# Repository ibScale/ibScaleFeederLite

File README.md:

# ibScaleFeederLite

`ibScaleFeederLite` is an updated version of the [Opulo LumenPNP Rev 12 Feeder](https://github.com/opulo-inc/feeder) motherboard with several enhancements.

## What's different from the Rev 12 motherboard

### PCB Stackup
The PCB is a 4-layer stackup with 7628 prepreg. The cost difference is negligible compared to the original 2-layer stackup. This allows for a cleaner layout with improved routing and component placement. The bottom layer of the PCB is kept as a ground layer only with no traces. Since this layer of the PCB is exposed it is very likely to get knicked, scratched, or otherwise damaged by the environment. This prevents any minor damage from affecting the operation of the feeder.

### DC/DC buck converter
The original OnSemi MC34063AD design used a 100µF input and 470µF output electrolytic capacitors. These capacitors are relatively expensive and difficult to source in low-profile heights suitable for the 8mm feeders. The large 100uF input capacitance would also cause arcing during insertion from the inrush current while charging. In addition to this, if the LumenPNP had 50 feeders plugged in the excessive bus capacitance would cause power sag (brown out) or potentially even trip the over-current protection. If the over-current protection does trip then the LumenPNP will boot loop as the 24V DC supply resets.

A Texas Instruments TPS563300 with MLCC capacitors has replaced the original design. The input capacitance has been reduced to 10uF to help prevent arcing during insertion. The reduced capacitance also helps mitigate the excessive bus capacitance start-up issue. A 0.75A PPTC fuse (F1) and diode (D1) have also been added to provide over-current and reverse-current protection.

### RS-485 transceiver
The AD/Maxim MAX3078E transceiver is the single most expensive component on the Opulo Rev12 feeder. Since the LumenPNP only operates at 57600bps there is no need to have an expensive part. The new TI THVD1400D transceiver is about 1/10th the cost and more then adequate for this application.

### Status LED
The RGB status LED has been changed to a Lite-On LTST-S33FBEGW-5A. This LED has a translucent diffuser and is designed for low current applications. It is available from a variety of suppliers and is an overall better quality indicator.

### Buttons
The original buttons were probably one of the biggest pain points on the original Rev12 design. These have been upgraded to Diptronics PTCF-V-T/R with J-hook stems. These switches are larger and available from a variety of suppliers. This along with improved debounce circuitry provide a better user experience.

### SWD connector
The original placement of the SWD connector made it difficult to use commonly available POGO pin clips like the Adafruit 5434. The connector was rotated and moved to the edge of the PCB to make using POGO pin clips easier.

## Hardware overview

| Function | Part |
|---|---|
| MCU | STM32F031C6T6 (Arm Cortex-M0, 48 MHz, 32 KB flash) |
| Motor drivers (Drive / Peel) | 2x TI DRV8837 |
| RS-485 transceiver | TI THVD1400D |
| Buck regulator | TI TPS563300 |
| Status LED | Lite-On LTST-S33FBEGW-5A |
| UP/DOWN/BOOT switches | Diptronics PTCF-V-T/R |

## Repository structure

```
ibScaleFeederLite/
├── ibScaleFeederLite.kicad_pro   KiCad project file
├── ibScaleFeederLite.kicad_pcb   PCB layout
├── ibScaleFeederLite.kicad_sch   Schematic
├── library/                      Project-specific symbols, footprints, and 3D models
└── references/                   Component datasheets
```

## Opening the project

Requires [KiCad](https://www.kicad.org/) 10 or newer. Open `ibScaleFeederLite.kicad_pro` to get started.

All custom symbols, footprints, and 3D models used by the project are included in `library/` and referenced via the project-local `sym-lib-table` and `fp-lib-table`, so no additional library setup is required.

## Bill of materials

Every component includes the manufacturer's name and part number, along with DigiKey, Mouser, and LCSC part numbers. To export a BOM, use KiCad's schematic editor: **Tools → Generate Bill of Materials**.

## License

Released under the [CERN Open Hardware Licence Version 2 - Strongly Reciprocal (CERN-OHL-S-2.0)](LICENSE.txt), consistent with the licensing of the original Opulo LumenPNP hardware it is derived from.

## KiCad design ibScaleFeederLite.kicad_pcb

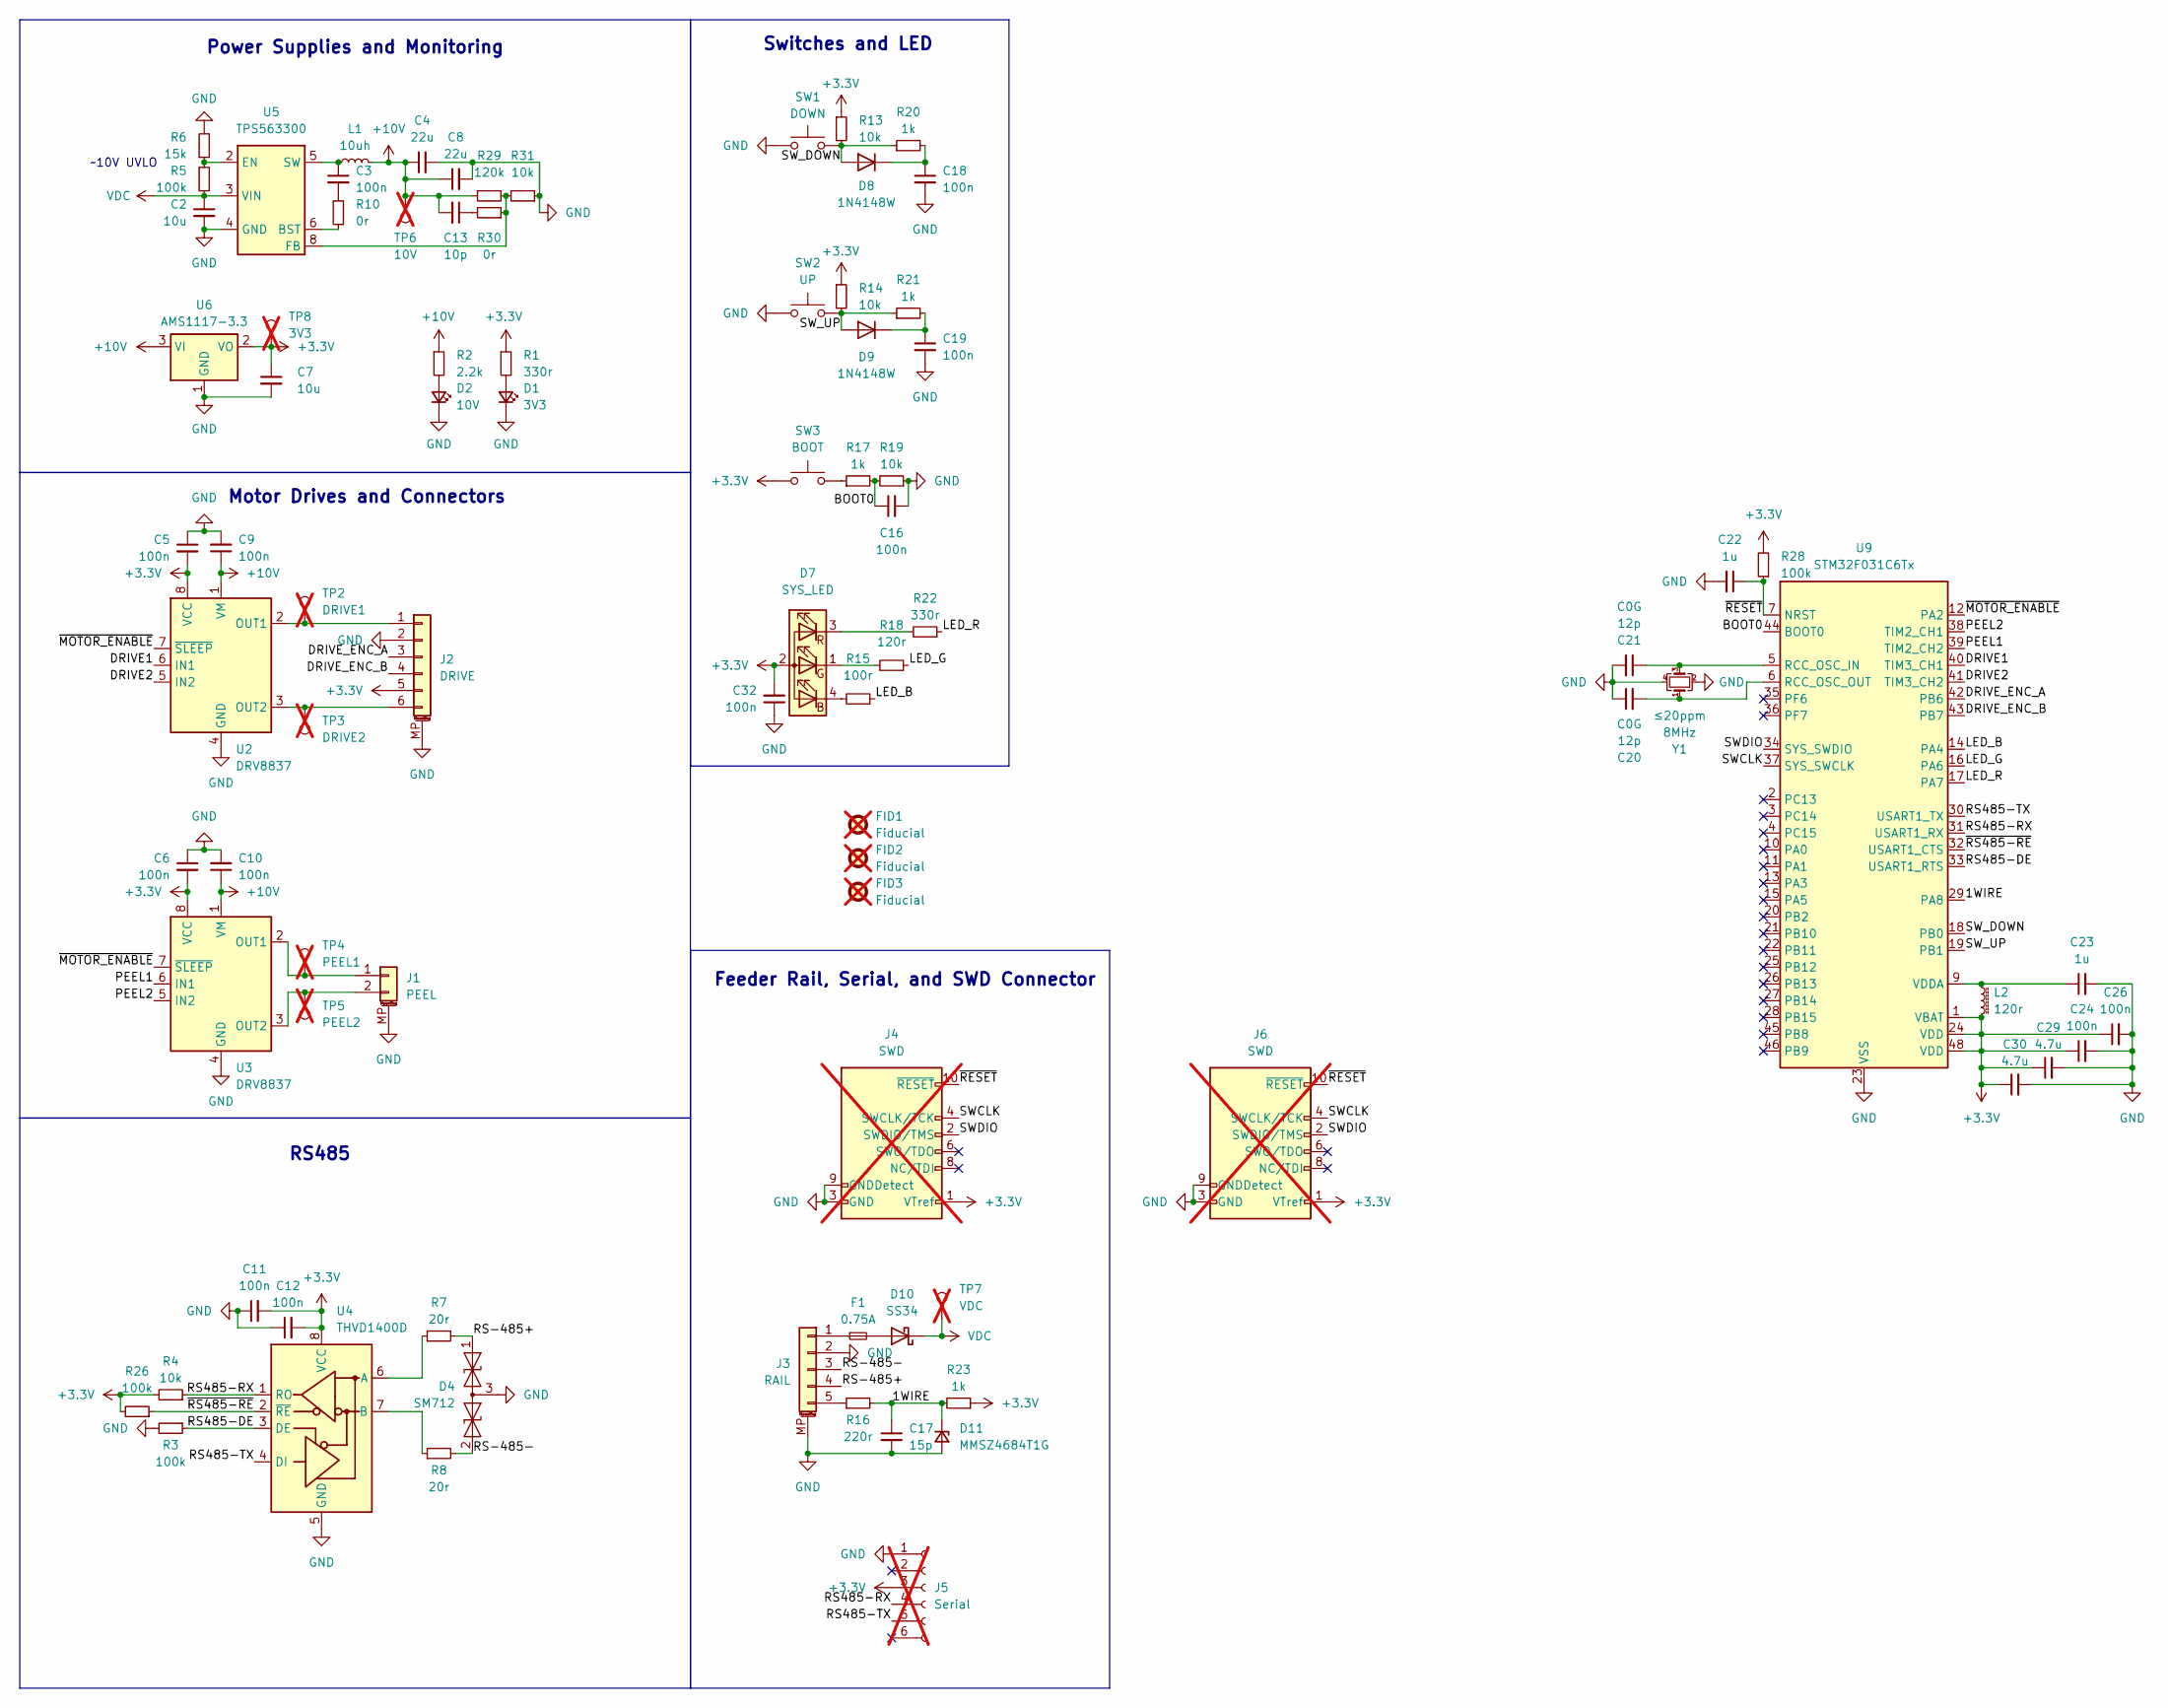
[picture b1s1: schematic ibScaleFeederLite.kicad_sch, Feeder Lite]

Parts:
C2: 10u; C_0805_2012Metric_Pad1.18x1.45mm_HandSolder; Tolerance X5R; Rating 50V; Manufacturer_Part GRM21BR61H106KE43L; Mouser 81-GRM21BR61H106KE3L
C3: 100n; C_0603_1608Metric_Pad1.08x0.95mm_HandSolder; Tolerance X5R; Rating 50V; Manufacturer_Part CC0603KRX7R9BB104; Mouser 603-CC603KRX7R9BB104
C4, C8: 22u; C_0805_2012Metric_Pad1.18x1.45mm_HandSolder; Tolerance X5R; Rating 25V; Manufacturer_Part CL21A226MAQNNNE; Mouser 187-CL21A226MAQNNNE
C5, C6, C9, C10, C11, C12, C24, C26: 100n; C_0603_1608Metric_Pad1.08x0.95mm_HandSolder; Manufacturer_Part CC0603KRX7R9BB104; LCSC C14663
C7: 10u; C_0805_2012Metric_Pad1.18x1.45mm_HandSolder; Manufacturer_Part GRM21BR61H106KE43L; LCSC C440198
C13: 10p; C_0603_1608Metric_Pad1.08x0.95mm_HandSolder; Tolerance CG0; Rating 25V; Manufacturer_Part CL10C100JB8NNNC; Mouser 187-CL10C100JB8NNNC
C16, C18, C19, C32: 100n; C_0603_1608Metric_Pad1.08x0.95mm_HandSolder; Manufacturer_Part CC0603KRX7R9BB104; DigiKey 311-1344-1-ND
C17: 15p; C_0603_1608Metric_Pad1.08x0.95mm_HandSolder; Manufacturer_Part CL10C150JB8NNNC; Mouser 187-CL10C150JB8NNNC
C20, C21: 12p; C_0603_1608Metric_Pad1.08x0.95mm_HandSolder; Rating C0G; Tolerance 1%; Manufacturer_Part CL10C120JB8NNNC; LCSC C38523
C22, C23: 1u; C_0603_1608Metric_Pad1.08x0.95mm_HandSolder; Manufacturer_Part CL10A105KB8NNNC; LCSC C15849
C29, C30: 4.7u; C_0603_1608Metric_Pad1.08x0.95mm_HandSolder; Manufacturer_Part CL10A475KO8NNNC; LCSC C19666
D1: 3V3; LED_0805_2012Metric_Pad1.15x1.40mm_HandSolder; Rating If=20ma, Vf=2.2v; Tolerance green; Manufacturer_Part LG R971-KN-1-0-20-R18; LCSC C2297
D2: 10V; LED_0805_2012Metric_Pad1.15x1.40mm_HandSolder; Rating If=20ma, Vf=2.2v; Tolerance green; Manufacturer_Part LG R971-KN-1-0-20-R18; LCSC C2297
D4: SM712; SOT-23; Manufacturer_Part SM712-02HTG; Mouser 576-SM712-02HTG
D7: SYS_LED; LED-SMD_4P-L3.0-W1.0-SIDE_LTST-S33FBEGW-5A; Manufacturer_Part LTST-S33FBEGW-5A; Mouser 859-LTST-S33FBEGW-5A
D8, D9: 1N4148W; D_SOD-123; Manufacturer_Part 1N4148WGW; LCSC C81598
D10: SS34; D_SMA; Manufacturer_Part SS34ALH; Mouser 821-SS34ALH
D11: MMSZ4684T1G; D_SOD-123; Manufacturer_Part MMSZ4684T1G; Mouser 863-MMSZ4684T1G
F1: 0.75A; Fuse_1812_4532Metric_Pad1.30x3.40mm_HandSolder; Manufacturer_Part PTS181233V075; Mouser 504-PTS181233V075
FID1, FID2, FID3: Fiducial; Fiducial_1mm_Mask2mm; not fitted
J1: PEEL; Molex_PicoBlade_53261-0271_1x02-1MP_P1.25mm_Horizontal; Manufacturer_Part 53261-0271; Mouser 538-53261-0271
J2: DRIVE; Molex_PicoBlade_53261-0671_1x06-1MP_P1.25mm_Horizontal; Manufacturer_Part 53048-0610; Mouser 538-53048-0610
J3: RAIL; 009155005541006; Manufacturer_Part 009155005541006; Mouser 581-009155005541006
J4, J6: SWD; PinHeader_2x05_P1.27mm_Vertical_SMD; not fitted
J5: Serial; PinHeader_1.27mm_1x06_FrictionFit; not fitted
L1: 10uh; L_TDK_VLS6045EX_VLS6045AF; Manufacturer_Part VLS6045EX-100M; Mouser 810-VLS6045EX-100M
L2: 120r; L_0603_1608Metric_Pad1.05x0.95mm_HandSolder; Manufacturer_Part MFBM1V1608-121-R; LCSC C14709
R1: 330r; R_0603_1608Metric_Pad0.98x0.95mm_HandSolder; Manufacturer_Part RC0603FR-13330RL; Mouser 603-RC0603FR-13330RL
R2: 2.2k; R_0603_1608Metric_Pad0.98x0.95mm_HandSolder; Manufacturer_Part RT0603FRE132K2L; LCSC C4190
R3, R26: 100k; R_0603_1608Metric_Pad0.98x0.95mm_HandSolder; Manufacturer_Part RC0603JR-13100KL; LCSC C25803
R4, R13, R14, R19: 10k; R_0603_1608Metric_Pad0.98x0.95mm_HandSolder; Manufacturer_Part RC0603FR-0710KP; LCSC C25804
R5, R28: 100k; R_0603_1608Metric_Pad0.98x0.95mm_HandSolder; Manufacturer_Part RC0603JR-13100KL; Mouser 603-RC0603JR-13100KL
R6: 15k; R_0603_1608Metric_Pad0.98x0.95mm_HandSolder; Manufacturer_Part WR06X153 JTL; Mouser 791-WR06X153JTL
R7, R8: 20r; R_0603_1608Metric_Pad0.98x0.95mm_HandSolder; Manufacturer_Part AC0603JR-0720RL; Mouser 603-AC0603JR-0720RL
R10, R30: 0r; R_0603_1608Metric_Pad0.98x0.95mm_HandSolder; Tolerance 1%; Manufacturer_Part RC0603FR-100RL; Mouser 603-RC0603FR-100RL
R15: 100r; R_0603_1608Metric_Pad0.98x0.95mm_HandSolder; Manufacturer_Part RK73H1JTTD1000F; LCSC C22775
R16: 220r; R_0603_1608Metric_Pad0.98x0.95mm_HandSolder; Manufacturer_Part RMCF0603JT220R; Mouser 708-RMCF0603JT220R
R17, R20, R21, R23: 1k; R_0603_1608Metric_Pad0.98x0.95mm_HandSolder; Manufacturer_Part RC0603FR-131KL; LCSC C21190
R18: 120r; R_0603_1608Metric_Pad0.98x0.95mm_HandSolder; Manufacturer_Part RMCF0603FT120R; LCSC C22787
R22: 330r; R_0603_1608Metric_Pad0.98x0.95mm_HandSolder; Manufacturer_Part RC0603FR-13330RL; LCSC C23138
R29: 120k; R_0603_1608Metric_Pad0.98x0.95mm_HandSolder; Tolerance 1%; Manufacturer_Part RC0603JR-07120KL; Mouser 603-RC0603JR-07120KL
R31: 10k; R_0603_1608Metric_Pad0.98x0.95mm_HandSolder; Tolerance 1%; Manufacturer_Part RC0603FR-0710KP; Mouser 603-RC0603FR-0710KP
SW1: DOWN; PTCFVTR; Manufacturer_Part PTCF-V-T/R; Mouser 113-PTCF-V-T/R
SW2: UP; PTCFVTR; Manufacturer_Part PTCF-V-T/R; Mouser 113-PTCF-V-T/R
SW3: BOOT; PTCFVTR; Manufacturer_Part PTCF-V-T/R; Mouser 113-PTCF-V-T/R
TP2: DRIVE1; TestPoint_Pad_D1.5mm; not fitted
TP3: DRIVE2; TestPoint_Pad_D1.5mm; not fitted
TP4: PEEL1; TestPoint_Pad_D1.5mm; not fitted
TP5: PEEL2; TestPoint_Pad_D1.5mm; not fitted
TP6: 10V; TestPoint_Pad_D1.5mm; not fitted
TP7: VDC; TestPoint_Pad_D1.5mm; not fitted
TP8: 3V3; TestPoint_Pad_D1.5mm; not fitted
U2, U3: DRV8837; WSON-8-1EP_2x2mm_P0.5mm_EP0.9x1.6mm_ThermalVias; Manufacturer_Part DRV8837DSGR; Mouser 595-DRV8837DSGR
U4: THVD1400D; SOIC-8_3.9x4.9mm_P1.27mm; Manufacturer_Part THVD1400DR; Mouser 595-THVD1400DR
U5: TPS563300; SOT-583-8; Manufacturer_Part TPS563300DRLR; Mouser 595-TPS563300DRLR
U6: AMS1117-3.3; SOT-223-3_TabPin2; Manufacturer_Part LM1117MPX-3.3/NOPB; Mouser 926-LM1117MPX3.3NOPB
U9: STM32F031C6Tx; LQFP-48_7x7mm_P0.5mm; Manufacturer_Part STM32F031C6T6TR; Mouser 511-STM32F031C6T6TR
Y1: 8MHz; Crystal_SMD_3225-4Pin_3.2x2.5mm_HandSoldering; Tolerance ≤20ppm; Manufacturer_Part ECS-80-8-33-JGN-TR3; LCSC C648984

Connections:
+3.3V: C5.2, C6.2, C7.1, C11.2, C12.2, C24.1, C26.1, C29.1, C30.1, C32.2, D7.2 (A), J2.5, J4.1 (VTref), J5.3, J6.1 (VTref), L2.2, R1.1, R4.2, R13.1, R14.1, R23.1, R26.2, R28.2, SW3.1, TP8.1 (1_1), U2.8 (VCC), U3.8 (VCC), U4.8 (VCC), U6.2 (VO), U9.1 (VBAT), U9.24 (VDD), U9.48 (VDD)
+10V: C4.1, C8.1, C9.1, C10.1, C13.2, L1.2, R2.1, R29.1, TP6.1 (1_1), U2.1 (VM), U3.1 (VM), U6.3 (VI)
/1WIRE: C17.1, D11.1 (K), R16.2, R23.2, U9.29 (PA8)
/BOOT0: C16.1, R17.2, R19.2, U9.44 (BOOT0)
/DRIVE1: U2.6 (IN1), U9.40 (TIM3_CH1)
/DRIVE2: U2.5 (IN2), U9.41 (TIM3_CH2)
/DRIVE_ENC_A: J2.3, U9.42 (PB6)
/DRIVE_ENC_B: J2.4, U9.43 (PB7)
/LED_B: R15.1, U9.14 (PA4)
/LED_G: R18.1, U9.16 (PA6)
/LED_R: R22.1, U9.17 (PA7)
/PEEL1: U3.6 (IN1), U9.39 (TIM2_CH2)
/PEEL2: U3.5 (IN2), U9.38 (TIM2_CH1)
/RS485-DE: R3.1, U4.3 (DE), U9.33 (USART1_RTS)
/RS485-RX: J5.4, R4.1, U4.1 (RO), U9.31 (USART1_RX)
/RS485-TX: J5.5, U4.4 (DI), U9.30 (USART1_TX)
/RS-485+: D4.1 (A1), J3.4, R7.2
/RS-485-: D4.2 (A2), J3.3, R8.2
/SWCLK: J4.4 (SWCLK/TCK), J6.4 (SWCLK/TCK), U9.37 (SYS_SWCLK)
/SWDIO: J4.2 (SWDIO/TMS), J6.2 (SWDIO/TMS), U9.34 (SYS_SWDIO)
/SW_DOWN: D8.2 (A), R13.2, R20.1, SW1.2, U9.18 (PB0)
/SW_UP: D9.2 (A), R14.2, R21.1, SW2.2, U9.19 (PB1)
/~MOTOR_ENABLE: U2.7 (~SLEEP), U3.7 (~SLEEP), U9.12 (PA2)
/~RESET: C22.1, J4.10 (~RESET), J6.10 (~RESET), R28.1, U9.7 (NRST)
/~RS485-RE: R26.1, U4.2 (~RE), U9.32 (USART1_CTS)
GND: C2.2, C4.2, C5.1, C6.1, C7.2, C8.2, C9.2, C10.2, C11.1, C12.1, C16.2, C17.2, C18.2, C19.2, C20.1, C21.2, C22.2, C23.2, C24.2, C26.2, C29.2, C30.2, C32.1, D1.1 (K), D2.1 (K), D4.3 (common), D11.2 (A), J1.MP (MountPin), J2.2, J2.MP (MountPin), J3.2, J3.MP (MountPin), J4.3 (GND), J4.5 (GND), J4.9 (GNDDetect), J5.1, J6.3 (GND), J6.5 (GND), J6.9 (GNDDetect), R3.2, R6.2, R19.1, R31.1, SW1.1, SW2.1, U2.4 (GND), U2.9 (GND), U3.4 (GND), U3.9 (GND), U4.5 (GND), U5.4 (GND), U6.1 (GND), U9.8 (VSSA), U9.23 (VSS), U9.47 (VSS), Y1.2, Y1.4
unnamed: C3.2, R10.2
unnamed: C13.1, R30.2
unnamed: D1.2 (A), R1.2
unnamed: D2.2 (A), R2.2
unnamed: D7.4 (BK), R15.2
unnamed: D7.1 (GK), R18.2
unnamed: D7.3 (RK), R22.2
unnamed: C18.1, D8.1 (K), R20.2
unnamed: C19.1, D9.1 (K), R21.2
unnamed: D10.2 (A), F1.2
unnamed: J1.1, TP4.1 (1_1), U3.2 (OUT1)
unnamed: J1.2, TP5.1 (1_1), U3.3 (OUT2)
unnamed: J2.1, TP2.1 (1_1), U2.2 (OUT1)
unnamed: J2.6, TP3.1 (1_1), U2.3 (OUT2)
unnamed: F1.1, J3.1
unnamed: J3.5, R16.1
unnamed: R17.1, SW3.2
unnamed: R7.1, U4.6 (A)
unnamed: R8.1, U4.7 (B)
unnamed: R10.1, U5.6 (BST)
unnamed: R5.1, R6.1, U5.2 (EN)
unnamed: R29.2, R30.1, R31.2, U5.8 (FB)
unnamed: C3.1, L1.1, U5.5 (SW)
unnamed: C21.1, U9.5 (RCC_OSC_IN), Y1.3
unnamed: C20.2, U9.6 (RCC_OSC_OUT), Y1.1
unnamed: C23.1, L2.1, U9.9 (VDDA)
VDC: C2.1, D10.1 (K), R5.2, TP7.1 (1_1), U5.3 (VIN)

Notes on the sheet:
~10V UVLO
RS485
Power Supplies and Monitoring
Feeder Rail, Serial, and SWD Connector
Motor Drives and Connectors
Switches and LED

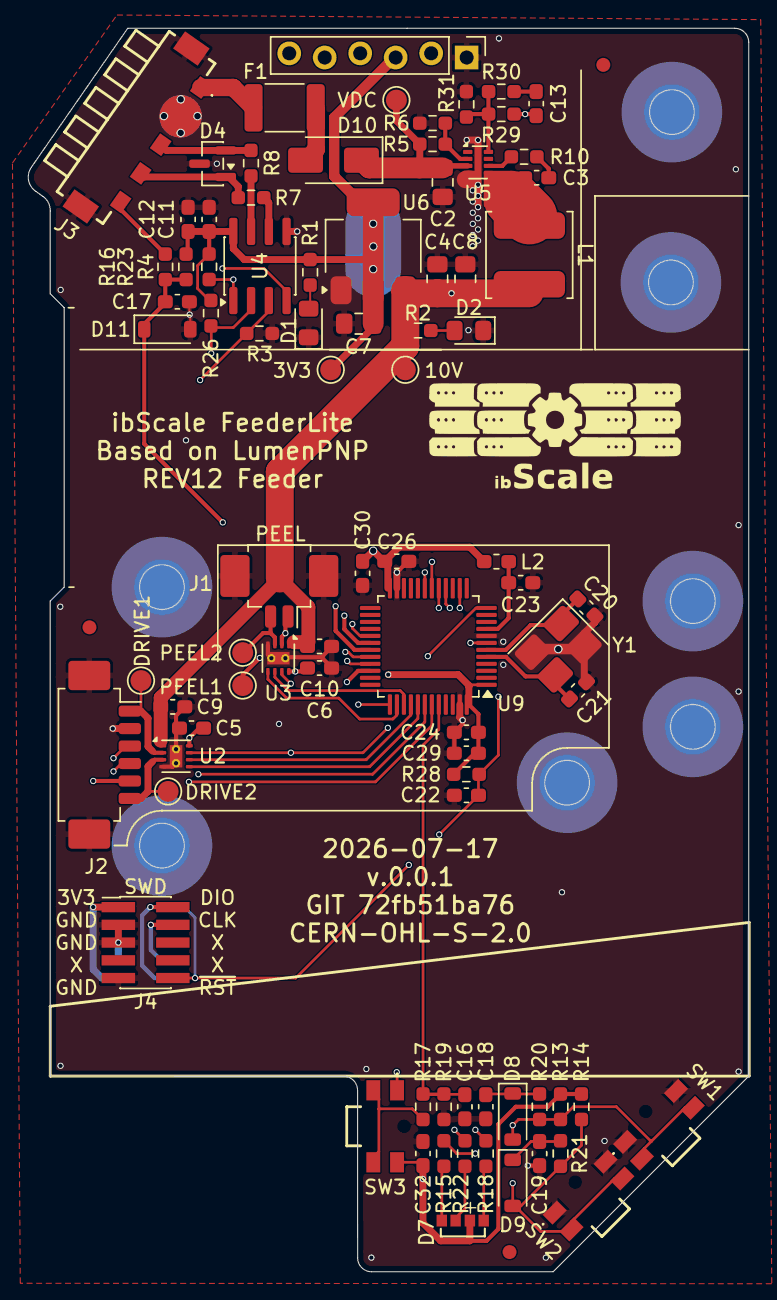
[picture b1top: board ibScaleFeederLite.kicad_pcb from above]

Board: 4 copper layers, 51.6 x 89.0 mm, 87 parts (1 on the bottom side), 53 nets.
